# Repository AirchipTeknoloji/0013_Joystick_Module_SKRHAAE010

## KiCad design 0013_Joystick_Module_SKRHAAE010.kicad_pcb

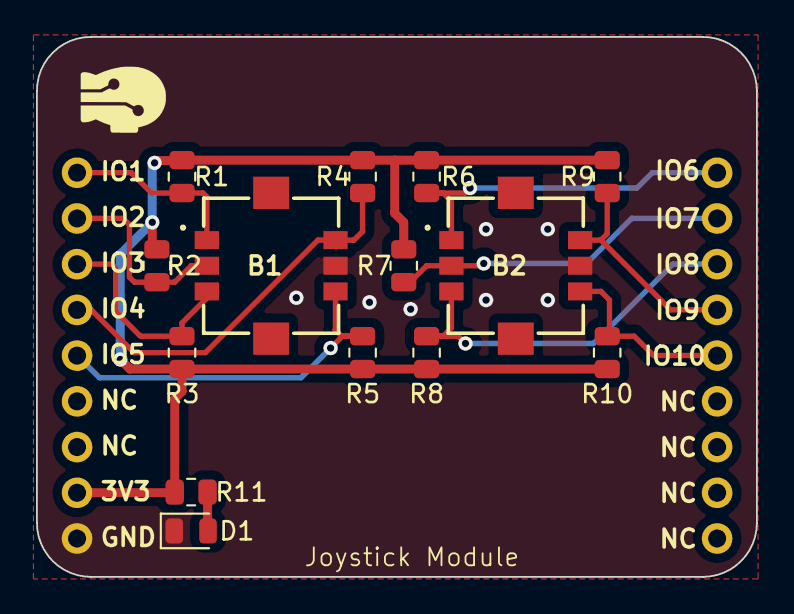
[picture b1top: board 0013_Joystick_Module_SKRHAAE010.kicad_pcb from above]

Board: 2 copper layers, 40.0 x 30.0 mm, 15 parts (0 on the bottom side), 13 nets.

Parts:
B1, B2: SKRHAAE010
D1: LED; LED_0805_2012Metric
R1, R2, R3, R4, R5, R6, R7, R8, R9, R10: 10k; R_0805_2012Metric
R11: R; R_0805_2012Metric
U1: air_module

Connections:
+3V3: R1.1, R2.1, R3.1, R4.2, R5.2, R6.1, R7.1, R8.1, R9.2, R10.2, R11.1, U1.8 (3V3)
/GPIO1: B1.1 (A), R1.2, U1.1 (MOSI)
/GPIO2: B1.2 (CENTER_PUSH), R2.2, U1.2 (MISO)
/GPIO3: B1.3 (C), R3.2, U1.3 (CS)
/GPIO4: B1.4 (B), R4.1, U1.4 (SCK)
/GPIO5: B1.6 (D), R5.1, U1.5 (SCL)
/GPIO6: B2.1 (A), R6.2, U1.18 (GPIO)
/GPIO7: B2.2 (CENTER_PUSH), R7.2, U1.17 (GPIO)
/GPIO8: B2.3 (C), R8.2, U1.16 (GPIO)
/GPIO9: B2.4 (B), R9.1, U1.15 (GPIO)
/GPIO10: B2.6 (D), R10.1, U1.14 (GPIO)
GND: B1.5 (COMMON), B2.5 (COMMON), D1.1 (K), U1.9 (GND)
unnamed: D1.2 (A), R11.2
